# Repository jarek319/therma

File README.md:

# therma
A Wifi-enabled Thermostat

I saw a motorized linear potentiometer on Sparkfun and had to get it. After watching something about Google's Nook, I wanted to see if I could design a Wifi enabled thermostat with a more classic left to right temperature-setting design.

The motorized functionality was used to add scheduling that moved the slider when the set temperature changes based on the schedule programmed.

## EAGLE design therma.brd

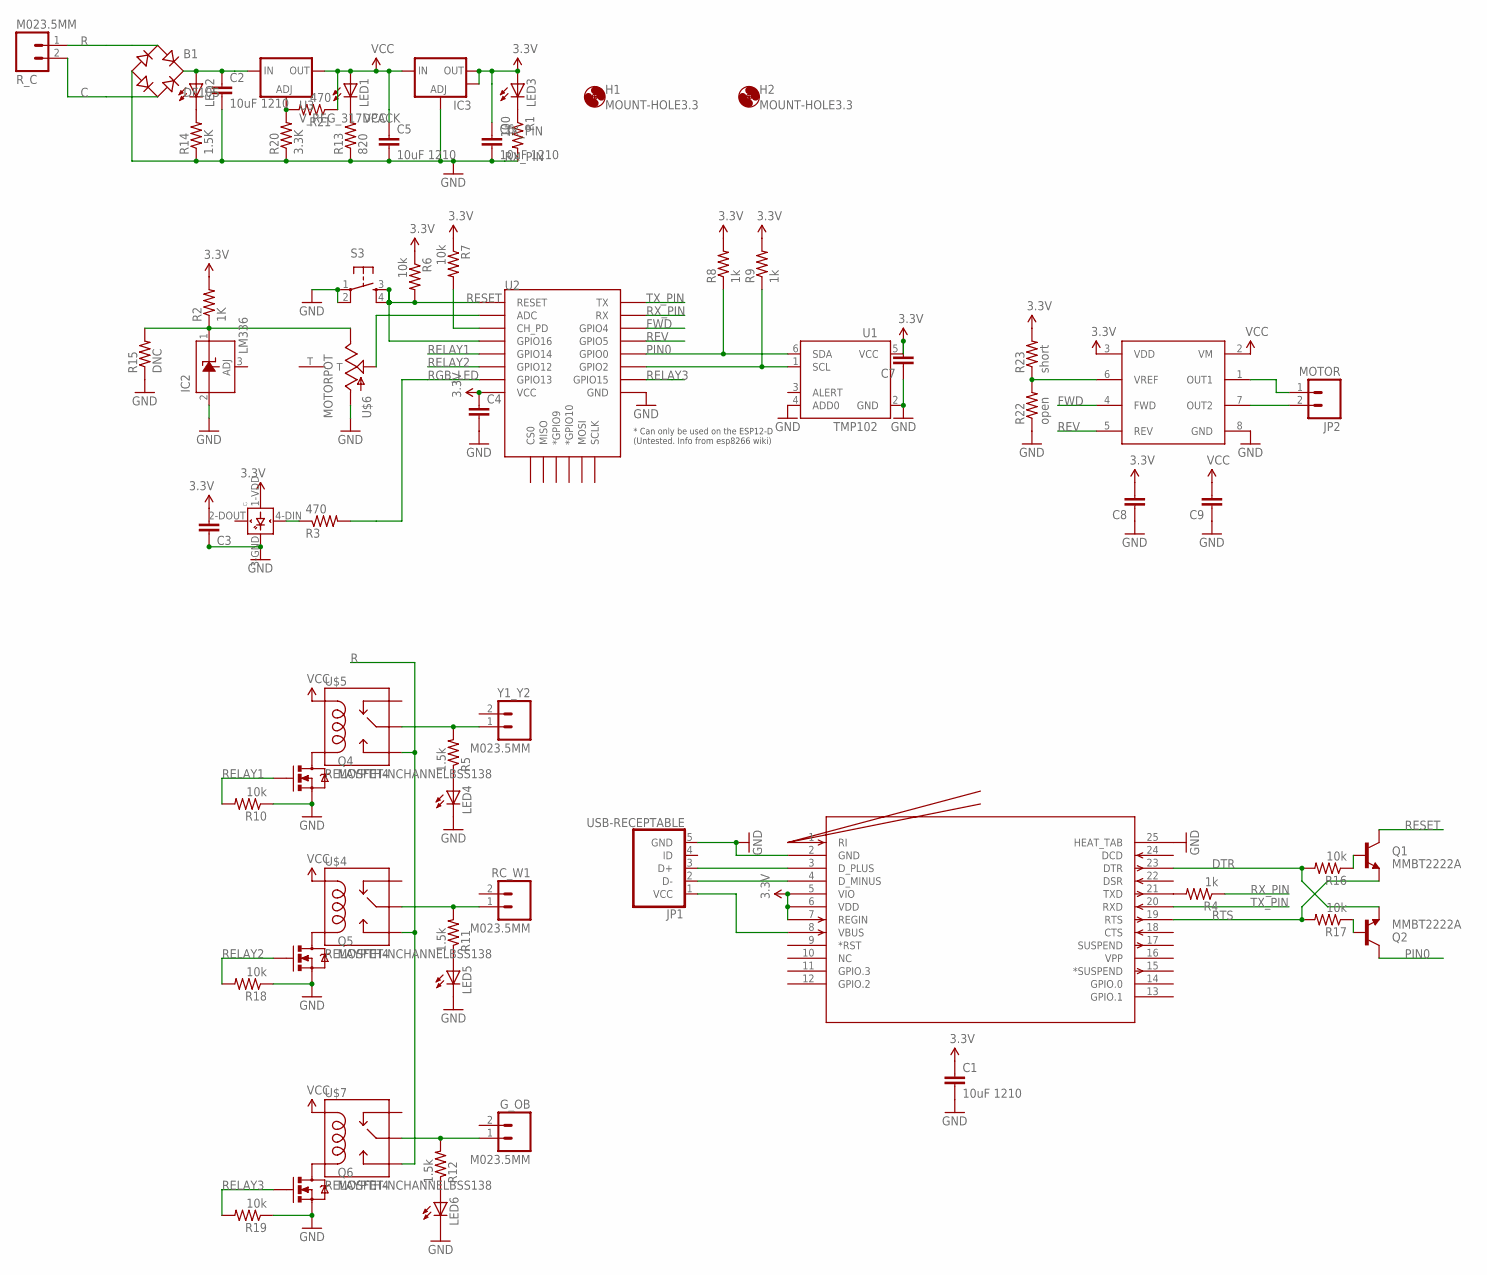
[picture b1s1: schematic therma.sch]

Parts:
B1: DF10S; DFS
C1, C2, C5, C6: 10uF 1210; 1210
C3, C4, C7, C8, C9: CAP0603-CAP; 0603-CAP
G_OB: M023.5MM; SCREWTERMINAL-3.5MM-2
H1, H2: MOUNT-HOLE3.3; 3,3
IC2: LM336; SOT23-3
IC3: V_REG_LM1117SOT223; SOT223
JP1: USB-RECEPTABLE; FCI-10103594-0001LF
JP2: MOTOR; 1X02
L2: WS2812B
LED1, LED2, LED3, LED4, LED5, LED6: LEDCHIPLED_1206; CHIPLED_1206
Q1, Q2: MMBT2222A; SOT23
Q4, Q5, Q6: MOSFET-NCHANNELBSS138; SOT23
R1: 100; R0603
R2: 1K; R0603
R3, R21: 470; R0603
R4, R8, R9: 1k; R0603
R5, R11, R12: 1.5k; R0603
R6, R7, R10, R16, R17, R18, R19: 10k; R0603
R13: 820; R0603
R14: 1.5K; R0603
R15: DNC; R0603
R20: 3.3K; R0603
R22: open; R0603
R23: short; R0603
RC_W1: M023.5MM; SCREWTERMINAL-3.5MM-2
R_C: M023.5MM; SCREWTERMINAL-3.5MM-2
S3: TAC_SWITCHSMD; TACTILE_SWITCH_SMD
U1: TMP102; SOT563
U2: ESP12ESMD; ESP12E-SMD
U3: V_REG_317DPACK; V-REG_DPACK
U$1: ZXBM5210SOIC; SOIC8
U$4, U$5, U$7: RELAYPTH4; RELAY-JZC
U$6: MOTORPOT; MOTORIZEDPOT
U$8: CP2104-GM; QFN24_4X4
Y1_Y2: M023.5MM; SCREWTERMINAL-3.5MM-2

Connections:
3.3V: C1.1, C3.2, C4.1, C6.1, C7.2, C8.2, IC3.2 (OUT), IC3.4 (OUT), L2.1-VDD (VDD), LED3.A, R2.2, R6.1, R7.1, R8.2, R9.2, R23.2, U1.5 (VCC), U2.VCC, U$1.3 (VDD), U$8.5 (VIO), U$8.6 (VDD), U$8.7 (REGIN)
C: B1.AC2, R_C.2
DTR: Q2.2 (E), R16.2, U$8.23 (DTR)
FWD: U2.GPIO4, U$1.4 (FWD)
GND: B1.-, C1.2, C2.2, C3.1, C4.2, C5.2, C6.2, C7.1, C8.1, C9.1, IC2.2 (A), IC3.1 (ADJ), JP1.5 (GND), L2.3-GND (GND), LED4.C, LED5.C, LED6.C, Q4.2 (S), Q5.2 (S), Q6.2 (S), R1.2, R10.1, R13.1, R14.1, R15.1, R18.1, R19.1, R20.1, R22.1, S3.1, S3.2, U1.2 (GND), U1.4 (ADD0), U2.GND, U$1.8 (GND), U$6.3' (3), U$8.2 (GND), U$8.25 (HEAT_TAB)
unnamed: Q4.3 (D), U$5.1 (COIL2)
unnamed: R7.2, U2.CH_PD
unnamed: R9.1, U1.1 (SCL), U2.GPIO2
unnamed: Q5.3 (D), U$4.1 (COIL2)
unnamed: Q6.3 (D), U$7.1 (COIL2)
unnamed: U2.ADC, U$6.2' (2)
unnamed: LED4.A, R5.1
unnamed: LED3.C, R1.1
unnamed: L2.4-DIN (DIN), R3.1
unnamed: JP1.1 (VCC), U$8.8 (VBUS)
unnamed: JP1.2 (D-), U$8.4 (D_MINUS)
unnamed: JP1.3 (D+), U$8.3 (D_PLUS)
unnamed: Q1.1 (B), R16.1
unnamed: IC2.1 (C), R2.1, R15.2, U$6.1' (1)
unnamed: R5.2, U$5.4 (MAIN), Y1_Y2.1
unnamed: G_OB.1, R12.2, U$7.4 (MAIN)
unnamed: R11.2, RC_W1.1, U$4.4 (MAIN)
unnamed: Q2.1 (B), R17.1
unnamed: LED5.A, R11.1
unnamed: LED6.A, R12.1
unnamed: R4.2, U$8.21 (TXD)
unnamed: R20.2, R21.2, U3.1 (ADJ)
unnamed: JP2.2, U$1.7 (OUT2)
unnamed: JP2.1, U$1.1 (OUT1)
unnamed: LED1.C, R13.2
unnamed: R22.2, R23.1, U$1.6 (VREF)
unnamed: B1.+, C2.1, LED2.A, U3.3 (IN)
unnamed: LED2.C, R14.2
PIN0: Q2.3 (C), R8.1, U1.6 (SDA), U2.GPIO0
R: B1.AC1, R_C.1, U$4.3 (NO), U$5.3 (NO), U$7.3 (NO)
RELAY1: Q4.1 (G), R10.2, U2.GPIO14
RELAY2: Q5.1 (G), R18.2, U2.GPIO12
RELAY3: Q6.1 (G), R19.2, U2.GPIO15
RESET: Q1.3 (C), R6.2, S3.3, S3.4, U2.GPIO16, U2.RESET
REV: U2.GPIO5, U$1.5 (REV)
RGB_LED: R3.2, U2.GPIO13
RTS: Q1.2 (E), R17.2, U$8.19 (RTS)
RX_PIN: R4.1, U2.RXD0 (RX)
TX_PIN: U2.TXD0 (TX), U$8.20 (RXD)
VCC: C5.1, C9.2, IC3.3 (IN), LED1.A, R21.1, U3.4 (OUT), U$1.2 (VM), U$4.5 (COIL1), U$5.5 (COIL1), U$7.5 (COIL1)

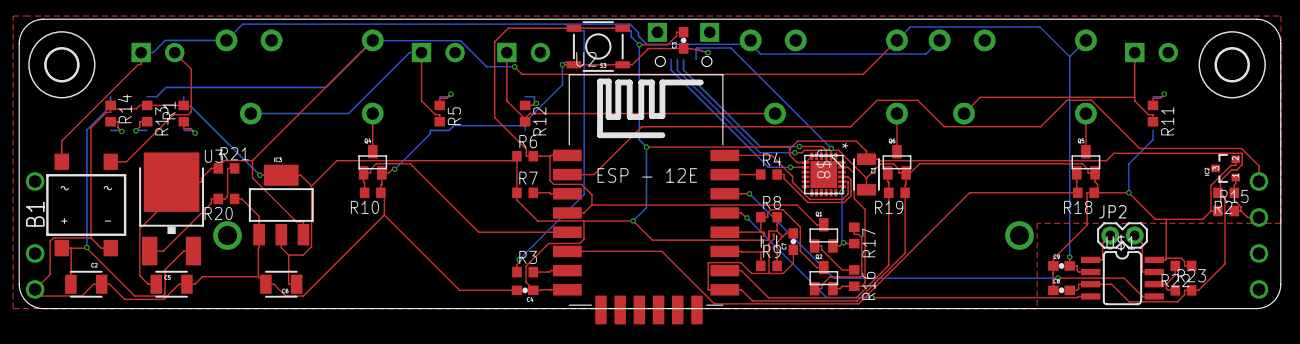
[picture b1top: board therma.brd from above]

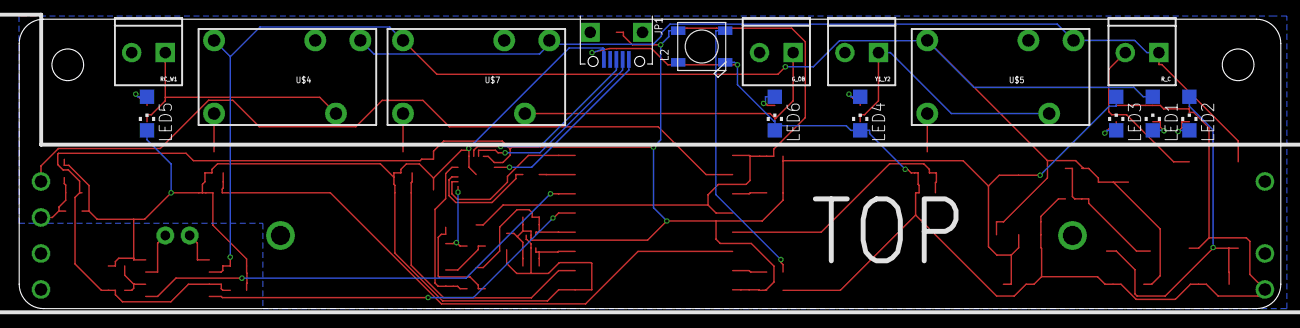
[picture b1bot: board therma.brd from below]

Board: 2 copper layers, 131.4 x 30.1 mm, 65 parts (16 on the bottom side), 45 nets.

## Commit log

2018-07-05 design tested: working

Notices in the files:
parts and their libraries:
SparkFun-Passives: Licensing: CC v3.0 Share-Alike You are welcome to use this library for commercial purposes.
